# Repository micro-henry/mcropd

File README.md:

# mcropd: ProMicro-compatible 3x3 macropad

## Features

- Kailh hotswap sockets
- 3x3 layout
- QMK firmware
- Per-key RGB & Underglow
- Rotary encoder
- OLED display
- Buzzer for audio
- Haptic feedback motor

## Images

> Top
> 
> Bottom
> 

PCB renders generated with a modified version (custom fonts) of [linalinn/kicad-render](https://github.com/linalinn/kicad-render)

## Parts

- 1x ProMicro (or compatible) microcontroller
- 9x Kailh hotswap sockets
- 9x 1n4148W SOT-123 diodes
- 1x 12mmx9.5mm Buzzer (optional)
- 3x 1uF 1206 capacitors (optional)
- 9x SK6812MINI-E Addressable RGB LEDs (optional)
- 4x WS2812B 5050 Addressable RGB LEDs (optional)
- 1x Push Button (optional)
- 1x EC11 Rotary Encoder & Knob (optional)
- 1x SH1106 SPI 7-pin OLED Display module & 2.54mmx7 PinHeader (optional)
- 1x 3V Haptic Feedback Motor (Module) & 2.54mmx3 PinHeader (optional)

## License

[CERN-OHL-S-2.0](https://ohwr.org/cern_ohl_s_v2.txt)

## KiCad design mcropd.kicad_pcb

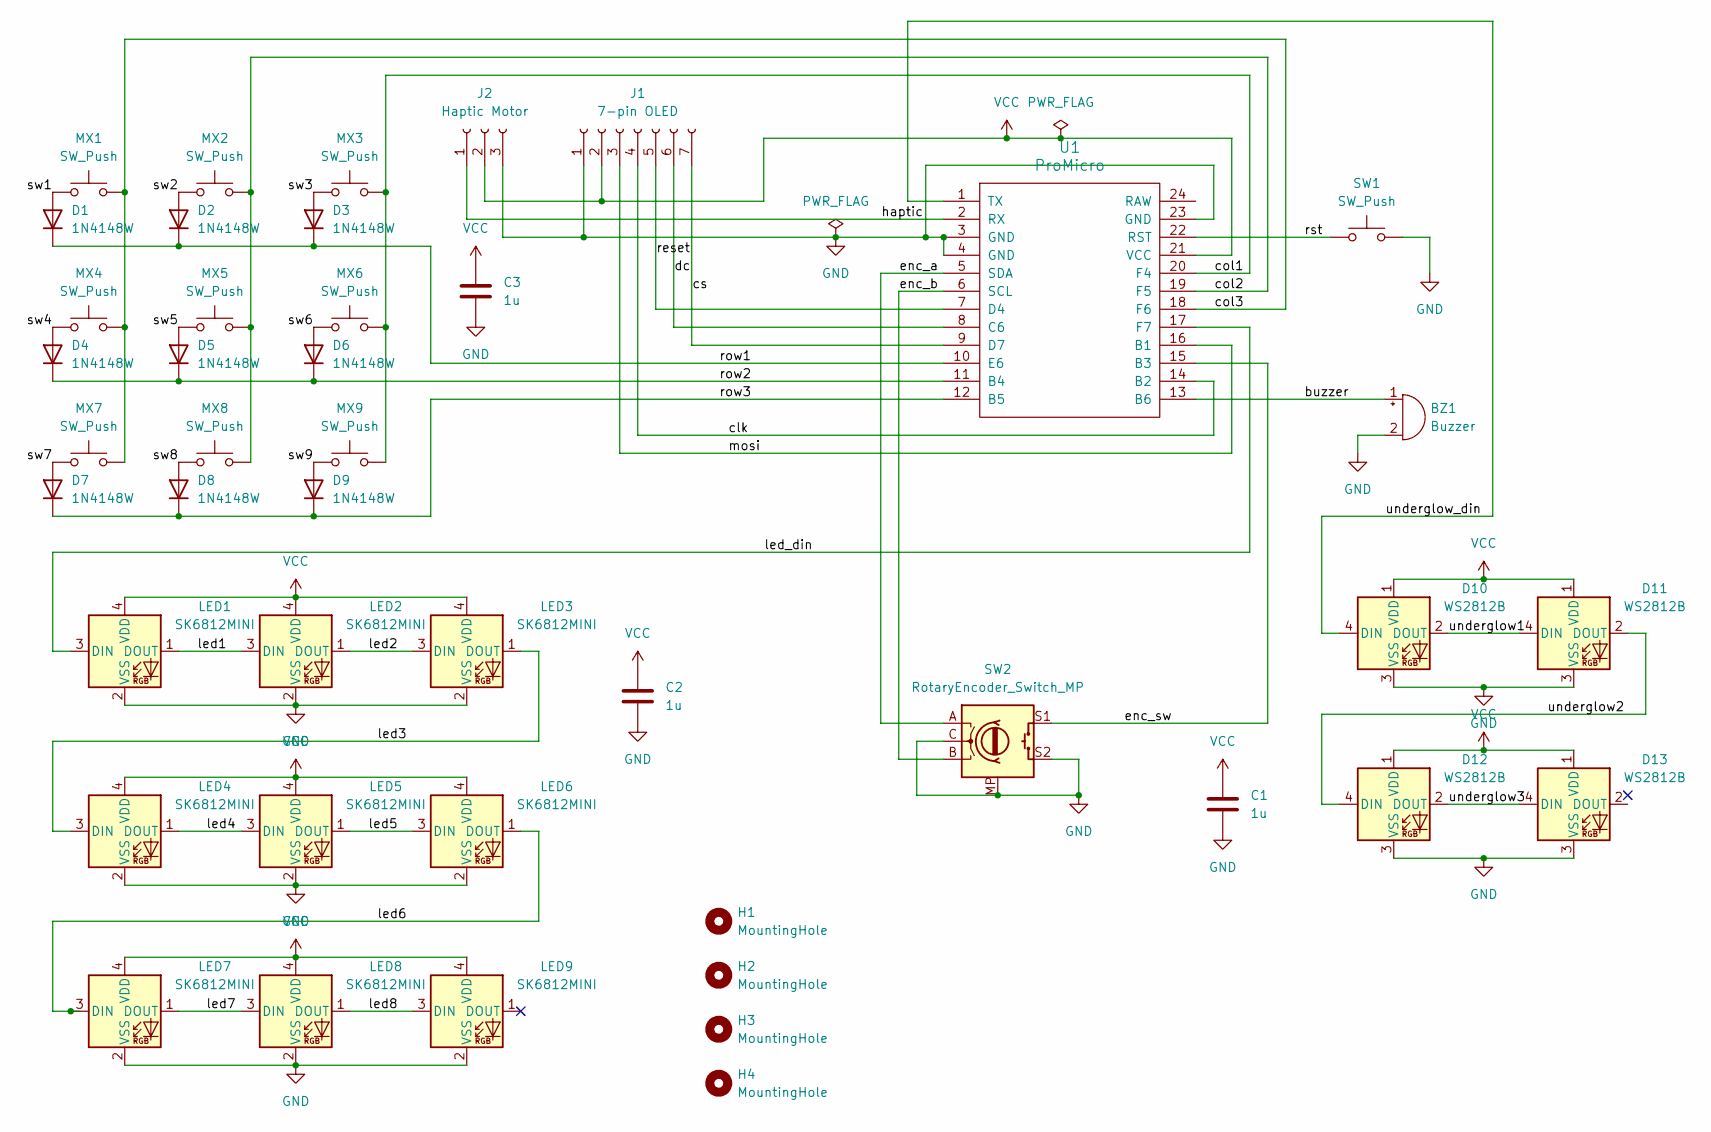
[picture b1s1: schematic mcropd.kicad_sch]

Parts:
BZ1: Buzzer; Buzzer_12x9.5RM7.6
C1, C2, C3: 1u; C_1206_3216Metric
D1, D2, D3, D4, D5, D6, D7, D8, D9: 1N4148W; D_SOD-123
D10, D11, D12, D13: WS2812B; LED_WS2812B_PLCC4_5.0x5.0mm_P3.2mm
H1, H2, H3, H4: MountingHole; MountingHole_3.2mm_M3
J1: 7-pin OLED; PinSocket_1x07_P2.54mm_Vertical
J2: Haptic Motor; PinSocket_1x03_P2.54mm_Vertical
LED1, LED2, LED3, LED4, LED5, LED6, LED7, LED8, LED9: SK6812MINI; MX_SK6812MINI-E_REV
MX1, MX2, MX3, MX4, MX5, MX6, MX7, MX8, MX9: SW_Push; SW_Hotswap_Kailh_MX_Plated_1.00u
SW1: SW_Push; SW_SPST_FSMSM
SW2: RotaryEncoder_Switch_MP; RotaryEncoder_Alps_EC11E-Switch_Vertical_H20mm
U1: ProMicro; ProMicro-NoSilk

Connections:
/buzzer: BZ1.1 (+), U1.13 (B6)
/clk: J1.4, U1.14 (B2)
/col1: MX3.2, MX6.2, MX9.2, U1.20 (F4)
/col2: MX2.2, MX5.2, MX8.2, U1.19 (F5)
/col3: MX1.2, MX4.2, MX7.2, U1.18 (F6)
/cs: J1.7, U1.9 (D7)
/dc: J1.6, U1.8 (C6)
/enc_a: SW2.A, U1.5 (SDA)
/enc_b: SW2.B, U1.6 (SCL)
/enc_sw: SW2.S1, U1.15 (B3)
/haptic: J2.1, U1.2 (RX)
/led1: LED1.1 (DOUT), LED2.3 (DIN)
/led2: LED2.1 (DOUT), LED3.3 (DIN)
/led3: LED3.1 (DOUT), LED4.3 (DIN)
/led4: LED4.1 (DOUT), LED5.3 (DIN)
/led5: LED5.1 (DOUT), LED6.3 (DIN)
/led6: LED6.1 (DOUT), LED7.3 (DIN)
/led7: LED7.1 (DOUT), LED8.3 (DIN)
/led8: LED8.1 (DOUT), LED9.3 (DIN)
/led_din: LED1.3 (DIN), U1.17 (F7)
/mosi: J1.3, U1.16 (B1)
/reset: J1.5, U1.7 (D4)
/row1: D1.1 (K), D2.1 (K), D3.1 (K), U1.10 (E6)
/row2: D4.1 (K), D5.1 (K), D6.1 (K), U1.11 (B4)
/row3: D7.1 (K), D8.1 (K), D9.1 (K), U1.12 (B5)
/rst: SW1.1, U1.22 (RST)
/sw1: D1.2 (A), MX1.1
/sw2: D2.2 (A), MX2.1
/sw3: D3.2 (A), MX3.1
/sw4: D4.2 (A), MX4.1
/sw5: D5.2 (A), MX5.1
/sw6: D6.2 (A), MX6.1
/sw7: D7.2 (A), MX7.1
/sw8: D8.2 (A), MX8.1
/sw9: D9.2 (A), MX9.1
/underglow1: D10.2 (DOUT), D11.4 (DIN)
/underglow2: D11.2 (DOUT), D12.4 (DIN)
/underglow3: D12.2 (DOUT), D13.4 (DIN)
/underglow_din: D10.4 (DIN), U1.1 (TX)
GND: BZ1.2 (-), C1.2, C2.2, C3.2, D10.3 (VSS), D11.3 (VSS), D12.3 (VSS), D13.3 (VSS), J1.1, J2.3, LED1.2 (VSS), LED2.2 (VSS), LED3.2 (VSS), LED4.2 (VSS), LED5.2 (VSS), LED6.2 (VSS), LED7.2 (VSS), LED8.2 (VSS), LED9.2 (VSS), SW1.2, SW2.C, SW2.MP, SW2.S2, U1.3 (GND), U1.4 (GND), U1.23 (GND)
VCC: C1.1, C2.1, C3.1, D10.1 (VDD), D11.1 (VDD), D12.1 (VDD), D13.1 (VDD), J1.2, J2.2, LED1.4 (VDD), LED2.4 (VDD), LED3.4 (VDD), LED4.4 (VDD), LED5.4 (VDD), LED6.4 (VDD), LED7.4 (VDD), LED8.4 (VDD), LED9.4 (VDD), U1.21 (VCC)

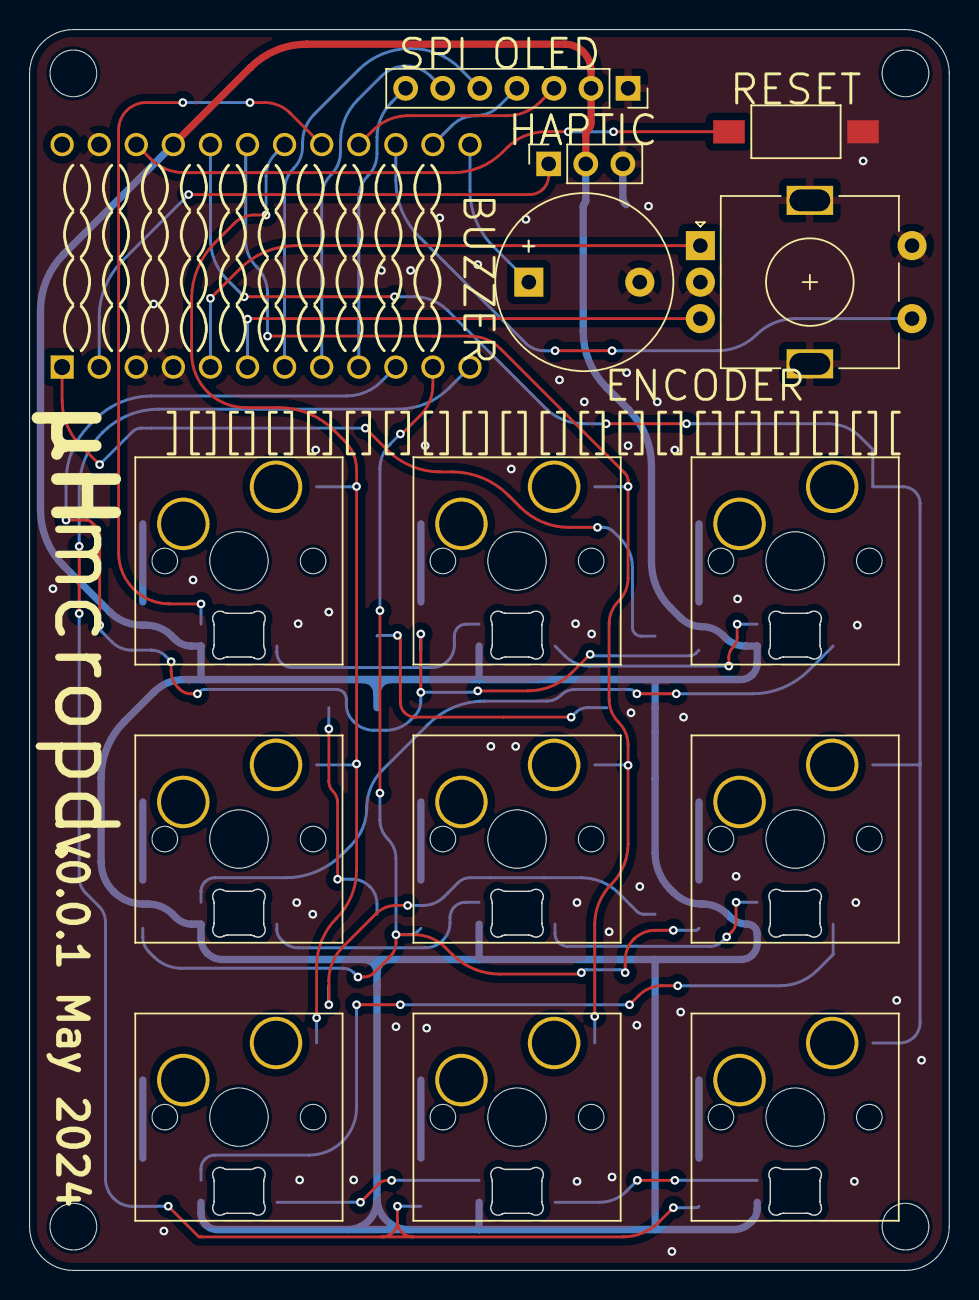
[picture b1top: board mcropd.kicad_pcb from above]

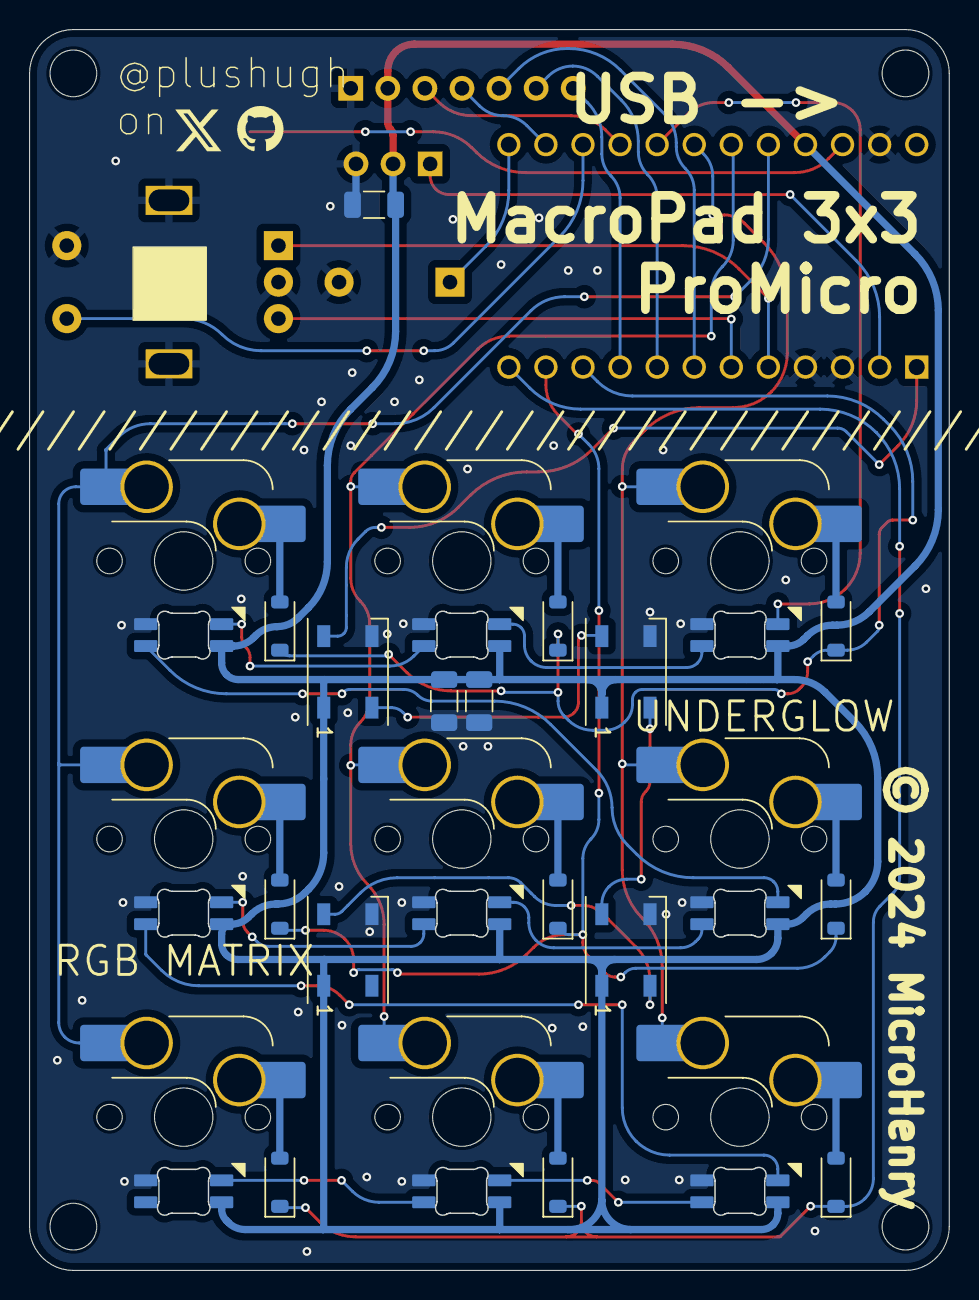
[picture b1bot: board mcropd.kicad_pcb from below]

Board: 2 copper layers, 62.9 x 85.0 mm, 44 parts (16 on the bottom side), 41 nets.

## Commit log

2024-05-14 init: add v0.0.1 files via upload
2024-05-14 init: setup kicad-render & README
2024-05-14 Create LICENSE

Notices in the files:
mcropd.kicad_pcb:
© 2024 MicroHenry
